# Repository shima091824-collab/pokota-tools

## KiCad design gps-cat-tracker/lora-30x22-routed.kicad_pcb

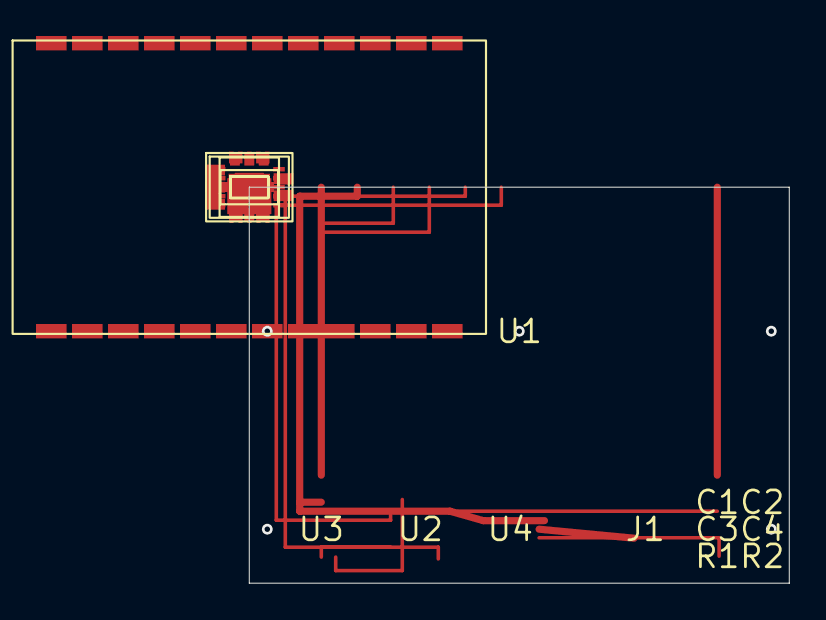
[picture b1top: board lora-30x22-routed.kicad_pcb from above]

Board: 2 copper layers, 30.0 x 22.0 mm, 11 parts (0 on the bottom side), 9 nets.

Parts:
C1, C2, C3, C4: 100nF
J1: JST-GH_1.25mm_2P
R1: 4.7k
R2: 10k
U1: E220-900T22S(JP)
U2: ATtiny3226
U3: MAX-M10S
U4: MCP73831T

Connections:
BATT_P: J1.1, U4.3
CHARGE_PROG: R1.1, U4.4
E220_AUX: R2.2, U1.7
GND: C1.2, C2.2, C3.2, C4.2, J1.2, R1.2, U1.1, U1.8, U1.9, U1.10, U1.11, U1.12, U1.13, U1.14, U1.15, U1.16, U1.17, U1.18, U1.19, U1.20, U1.21, U1.22, U1.23, U1.24, U2.1, U2.2, U2.3, U2.4, U2.7, U2.8, U2.9, U2.12, U2.13, U2.14, U2.15, U2.17, U2.18, U2.19, U2.20, U2.EP, U3.1, U3.5, U3.6, U3.7, U3.8, U3.9, U3.10, U3.EP, U4.1, U4.2
GPS_RXD: U2.10, U3.2
GPS_TXD: U2.11, U3.3
UART_RX: U1.6, U2.6
UART_TX: U1.5, U2.5
VCC_3V3: C1.1, C2.1, C3.1, C4.1, R2.1, U1.2, U2.16, U3.4, U4.5
